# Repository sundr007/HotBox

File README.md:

# HotBox

I use this when I'm testing electronics on my benchtop.  I put this box on top of what I'm testing to raise the ambient temperature.  This is convenient because I can leave my probes and other wires hooked up as is.
This box can raise the ambient temperature up to 55C.

The design consists of a finger edge laser cut acrylic box that has a circuit board assembly mount in the top center of it.  I put foam on the bottom edge of the box so it can nicely sit on top of wires and cables without air gaps.  

The circuit board assembly consists of a 2 layer PCB meant to fit PCBWAY's cheap board special (hint,they're $1 a piece for QTY 5).  On the PCB there is a ST NUCLEO-G431KB board which is an easy way to add a microcontroller.  There's 2 buttons to control temperature setpoint, a 7 segment display to display temperature, a peltier plate that acts as the heating element, and an Intel LGA1155 processor fan to spread the heat from the peltier plate.

I have built the current revision and found that it works as expected and I'm able to use it as I debug and test my electronics.

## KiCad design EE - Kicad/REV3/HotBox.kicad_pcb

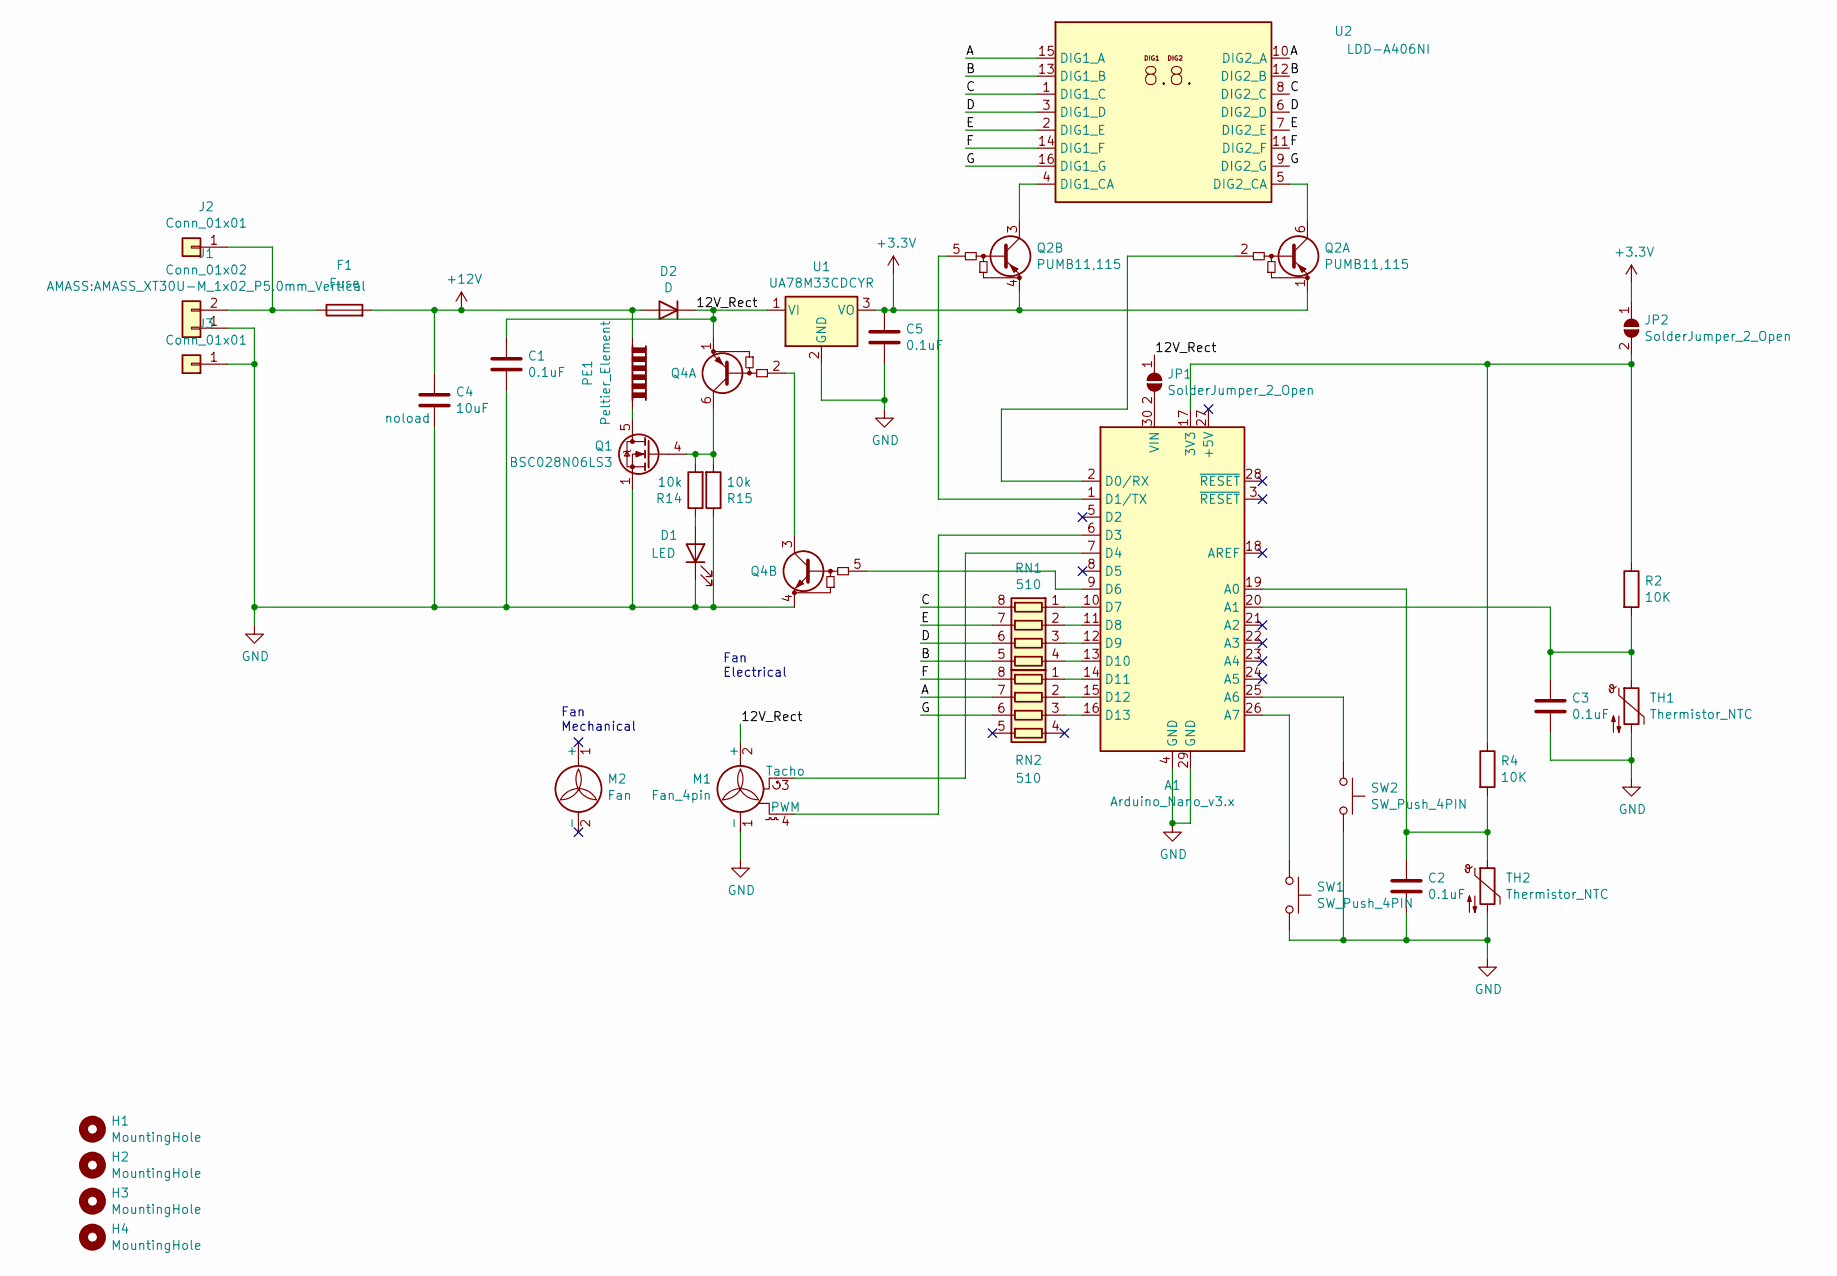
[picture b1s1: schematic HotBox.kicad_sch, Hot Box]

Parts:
A1: Arduino_Nano_v3.x; Arduino_Nano; DigikeyPN 497-19489-ND
C1, C2, C3, C5: 0.1uF; 0805_C; DigikeyPN 478-12790-1-ND
C4: 10uF; CP_Radial_D6.3mm_P2.50mm; DigikeyPN 493-16595-ND
D1: LED; LED_0603_1608Metric; DigikeyPN 732-4978-1-ND
D2: D; D_SMA; DigikeyPN SS13-LTPMSCT-ND
F1: Fuse; R_1206_3216Metric; DigikeyPN SF-1206HH10M-2CT-ND
H1, H2, H3, H4: MountingHole; MountingHole_3.2mm_M3; DigikeyPN 335-1156-ND
J1: Conn_01x02; AMASS_XT30U-M_1x02_P5.0mm_Vertical; DigikeyPN Amass XT30
J2, J3: Conn_01x01; Banana_Jack_1Pin; DigikeyPN 36-575-4-ND
JP1, JP2: SolderJumper_2_Open; SolderJumper-2_P1.3mm_Open_TrianglePad1.0x1.5mm
M1: Fan_4pin; FanPinHeader_1x04_P2.54mm_Vertical; DigikeyPN S1012EC-04-ND
M2: Fan; LGA1155_FAN; DigikeyPN Intel E98290-001
PE1: Peltier_Element; Peltier_40x40; DigikeyPN TEC1-12706
Q1: BSC028N06LS3; TDSON-8-1; DigikeyPN 1727-5435-1-ND
Q2: PUMB11,115; SOT-363_SC-70-6_Handsoldering; DigikeyPN 1727-5230-1-ND
Q4: PUMD3,115; SOT-363_SC-70-6_Handsoldering; DigikeyPN 1727-1984-1-ND
R2, R4: 10K; 0805_R; DigikeyPN 541-4163-1-ND
R14, R15: 10k; 0805_R; DigikeyPN 541-4163-1-ND
RN1, RN2: 510; R_Array_Convex_4x0603; DigikeyPN YC164J-510CT-ND
SW1, SW2: SW_Push_4PIN; SW_D6; DigikeyPN 401-1994-ND
TH1: Thermistor_NTC; 0805_R; DigikeyPN 445-175460-1-ND
TH2: Thermistor_NTC; SolderWire-0.25sqmm_1x02_P4.2mm_D0.65mm_OD1.7mm; DigikeyPN 445-175460-1-ND
U1: UA78M33CDCYR; SOT-223-3_TabPin2; DigikeyPN 296-13424-1-ND
U2: LDD-A406NI; DA04-11CGKWA; DigikeyPN 67-1447-ND

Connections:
+3V3: C5.1, JP2.1 (A), Q2.1 (E1), Q2.4 (E2), U1.3 (VO)
+12V: C4.1, D2.2 (A), F1.2, PE1.1
/12V_Rect: C1.1, D2.1 (K), JP1.1 (A), M1.2 (+), Q4.1 (E1), U1.1 (VI)
/A: RN2.7 (R2.2), U2.10 (DIG2_A), U2.15 (DIG1_A)
/B: RN1.5 (R4.2), U2.12 (DIG2_B), U2.13 (DIG1_B)
/C: RN1.8 (R1.2), U2.1 (DIG1_C), U2.8 (DIG2_C)
/D: RN1.6 (R3.2), U2.3 (DIG1_D), U2.6 (DIG2_D)
/E: RN1.7 (R2.2), U2.2 (DIG1_E), U2.7 (DIG2_E)
/F: RN2.8 (R1.2), U2.11 (DIG2_F), U2.14 (DIG1_F)
/G: RN2.6 (R3.2), U2.9 (DIG2_G), U2.16 (DIG1_G)
GND: A1.4 (GND), A1.29 (GND), C1.2, C2.2, C3.2, C4.2, C5.2, D1.1 (K), J1.1, J3.1, M1.1 (-), Q1.1 (S), Q1.2 (S), Q1.3 (S), Q4.4 (E1), R15.1, SW1.2, SW2.2, TH1.2, TH2.2, U1.2 (GND)
unnamed: A1.1 (D1/TX), Q2.5 (B2)
unnamed: A1.2 (D0/RX), Q2.2 (B1)
unnamed: A1.6 (D3), M1.4 (PWM)
unnamed: A1.7 (D4), M1.3 (Tacho)
unnamed: A1.9 (D6), Q4.5 (B1)
unnamed: A1.10 (D7), RN1.1 (R1.1)
unnamed: A1.11 (D8), RN1.2 (R2.1)
unnamed: A1.12 (D9), RN1.3 (R3.1)
unnamed: A1.13 (D10), RN1.4 (R4.1)
unnamed: A1.14 (D11), RN2.1 (R1.1)
unnamed: A1.15 (D12), RN2.2 (R2.1)
unnamed: A1.16 (D13), RN2.3 (R3.1)
unnamed: A1.17 (3V3), JP2.2 (B), R2.1, R4.1
unnamed: A1.19 (A0), C2.1, R4.2, TH2.1
unnamed: A1.20 (A1), C3.1, R2.2, TH1.1
unnamed: A1.25 (A6), SW2.1
unnamed: A1.26 (A7), SW1.1
unnamed: A1.30 (VIN), JP1.2 (B)
unnamed: D1.2 (A), R14.1
unnamed: F1.1, J1.2, J2.1
unnamed: PE1.2, Q1.5 (D)
unnamed: Q1.4 (G), Q4.6 (C1), R14.2, R15.2
unnamed: Q2.3 (C2), U2.4 (DIG1_CA)
unnamed: Q2.6 (C1), U2.5 (DIG2_CA)
unnamed: Q4.2 (B1), Q4.3 (C1)

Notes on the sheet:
Fan Mechanical
Fan Electrical

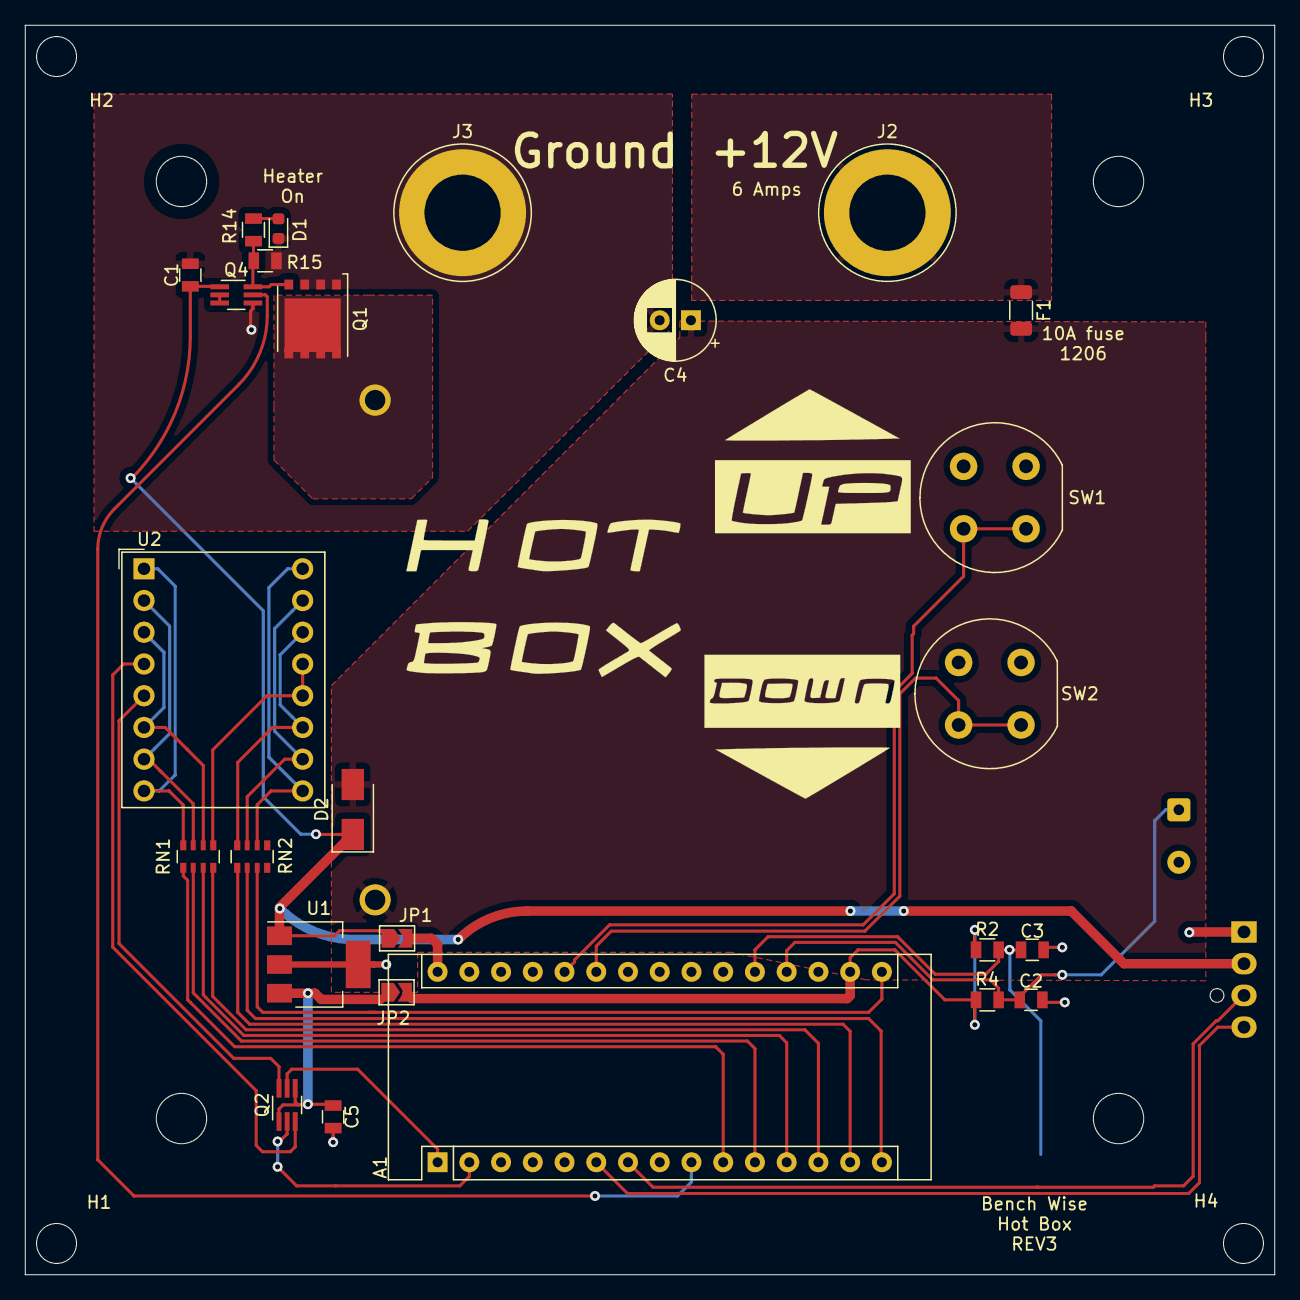
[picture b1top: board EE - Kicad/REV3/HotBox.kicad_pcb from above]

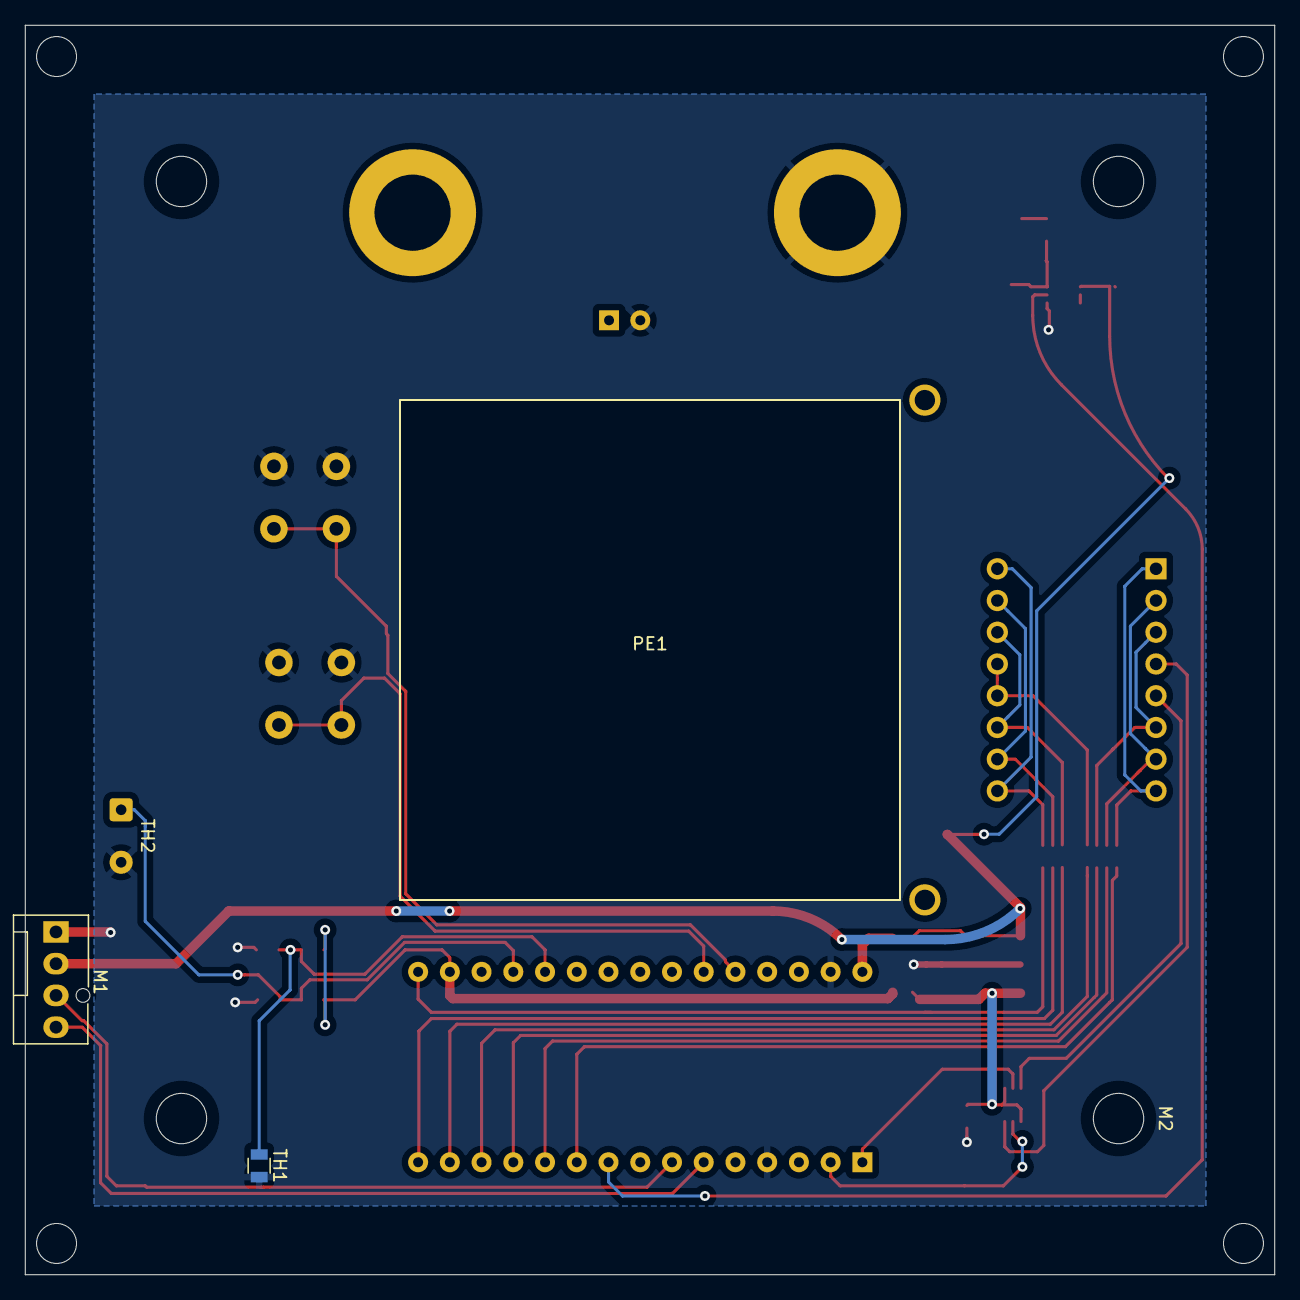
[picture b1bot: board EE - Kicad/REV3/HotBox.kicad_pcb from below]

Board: 2 copper layers, 100.0 x 100.0 mm, 35 parts (5 on the bottom side), 36 nets.

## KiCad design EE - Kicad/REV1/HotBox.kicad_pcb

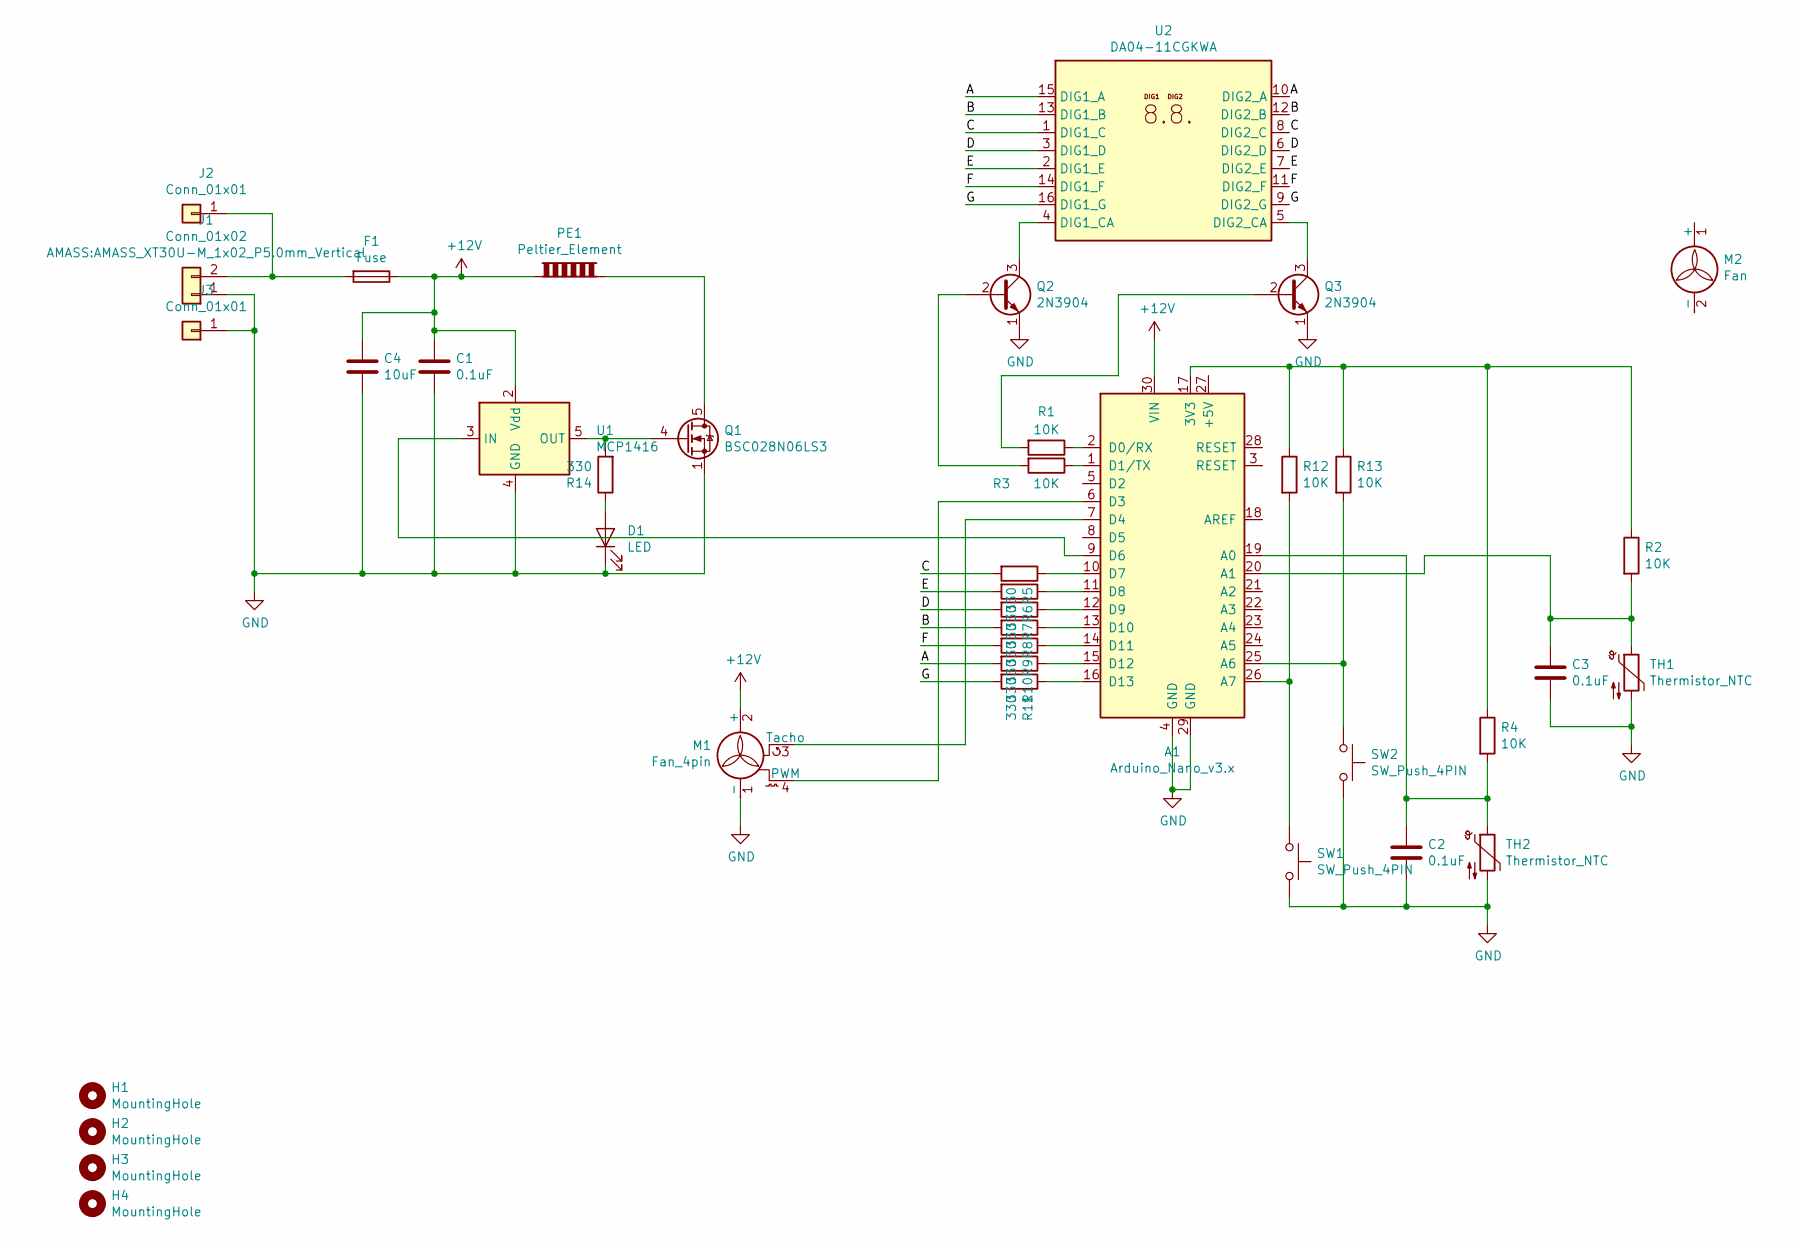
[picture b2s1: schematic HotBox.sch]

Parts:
A1: Arduino_Nano_v3.x; Arduino_Nano
C1, C2, C3: 0.1uF; 0805_C
C4: 10uF; CP_Radial_D6.3mm_P2.50mm
D1: LED; LED_0603_1608Metric
F1: Fuse; 1206_R
H1, H2, H3, H4: MountingHole; MountingHole_3.2mm_M3
J1: Conn_01x02; AMASS_XT30U-M_1x02_P5.0mm_Vertical
J2, J3: Conn_01x01; Banana_Jack_1Pin
M1: Fan_4pin; FanPinHeader_1x04_P2.54mm_Vertical
M2: Fan; LGA1155_FAN
PE1: Peltier_Element; Peltier_40x40
Q1: BSC028N06LS3; TDSON-8-1
Q2, Q3: 2N3904; SOT-23
R1, R2, R3, R4, R12, R13: 10K; 0805_R
R5, R6, R7, R8, R9, R10, R11, R14: 330; 0805_R
SW1, SW2: SW_Push_4PIN; SW_D6; DigikeyPN 401-1994-ND
TH1, TH2: Thermistor_NTC; 0805_R
U1: MCP1416; SOT-23-5
U2: DA04-11CGKWA

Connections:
+12V: A1.30 (VIN), C1.1, C4.1, F1.1, M1.2 (+), PE1.1, U1.2 (Vdd)
/A: R10.2, U2.10 (DIG2_A), U2.15 (DIG1_A)
/B: R8.2, U2.12 (DIG2_B), U2.13 (DIG1_B)
/C: R5.2, U2.1 (DIG1_C), U2.8 (DIG2_C)
/D: R7.2, U2.3 (DIG1_D), U2.6 (DIG2_D)
/E: R6.2, U2.2 (DIG1_E), U2.7 (DIG2_E)
/F: R9.2, U2.11 (DIG2_F), U2.14 (DIG1_F)
/G: R11.2, U2.9 (DIG2_G), U2.16 (DIG1_G)
GND: A1.4 (GND), A1.29 (GND), C1.2, C2.2, C3.2, C4.2, D1.1 (K), J1.1, J3.1, M1.1 (-), Q1.1 (S), Q1.2 (S), Q1.3 (S), Q2.1 (E), Q3.1 (E), SW1.2, SW2.2, TH1.2, TH2.2, U1.4 (GND)
unnamed: A1.1 (D1/TX), R3.1
unnamed: A1.2 (D0/RX), R1.1
unnamed: A1.6 (D3), M1.4 (PWM)
unnamed: A1.7 (D4), M1.3 (Tacho)
unnamed: A1.9 (D6), U1.3 (IN)
unnamed: A1.10 (D7), R5.1
unnamed: A1.11 (D8), R6.1
unnamed: A1.12 (D9), R7.1
unnamed: A1.13 (D10), R8.1
unnamed: A1.14 (D11), R9.1
unnamed: A1.15 (D12), R10.1
unnamed: A1.16 (D13), R11.1
unnamed: A1.17 (3V3), R2.1, R4.1, R12.1, R13.1
unnamed: A1.19 (A0), C2.1, R4.2, TH2.1
unnamed: A1.20 (A1), C3.1, R2.2, TH1.1
unnamed: A1.25 (A6), R13.2, SW2.1
unnamed: A1.26 (A7), R12.2, SW1.1
unnamed: D1.2 (A), R14.1
unnamed: F1.2, J1.2, J2.1
unnamed: PE1.2, Q1.5 (D)
unnamed: Q1.4 (G), R14.2, U1.5 (OUT)
unnamed: Q2.2 (B), R3.2
unnamed: Q2.3 (C), U2.4 (DIG1_CA)
unnamed: Q3.2 (B), R1.2
unnamed: Q3.3 (C), U2.5 (DIG2_CA)

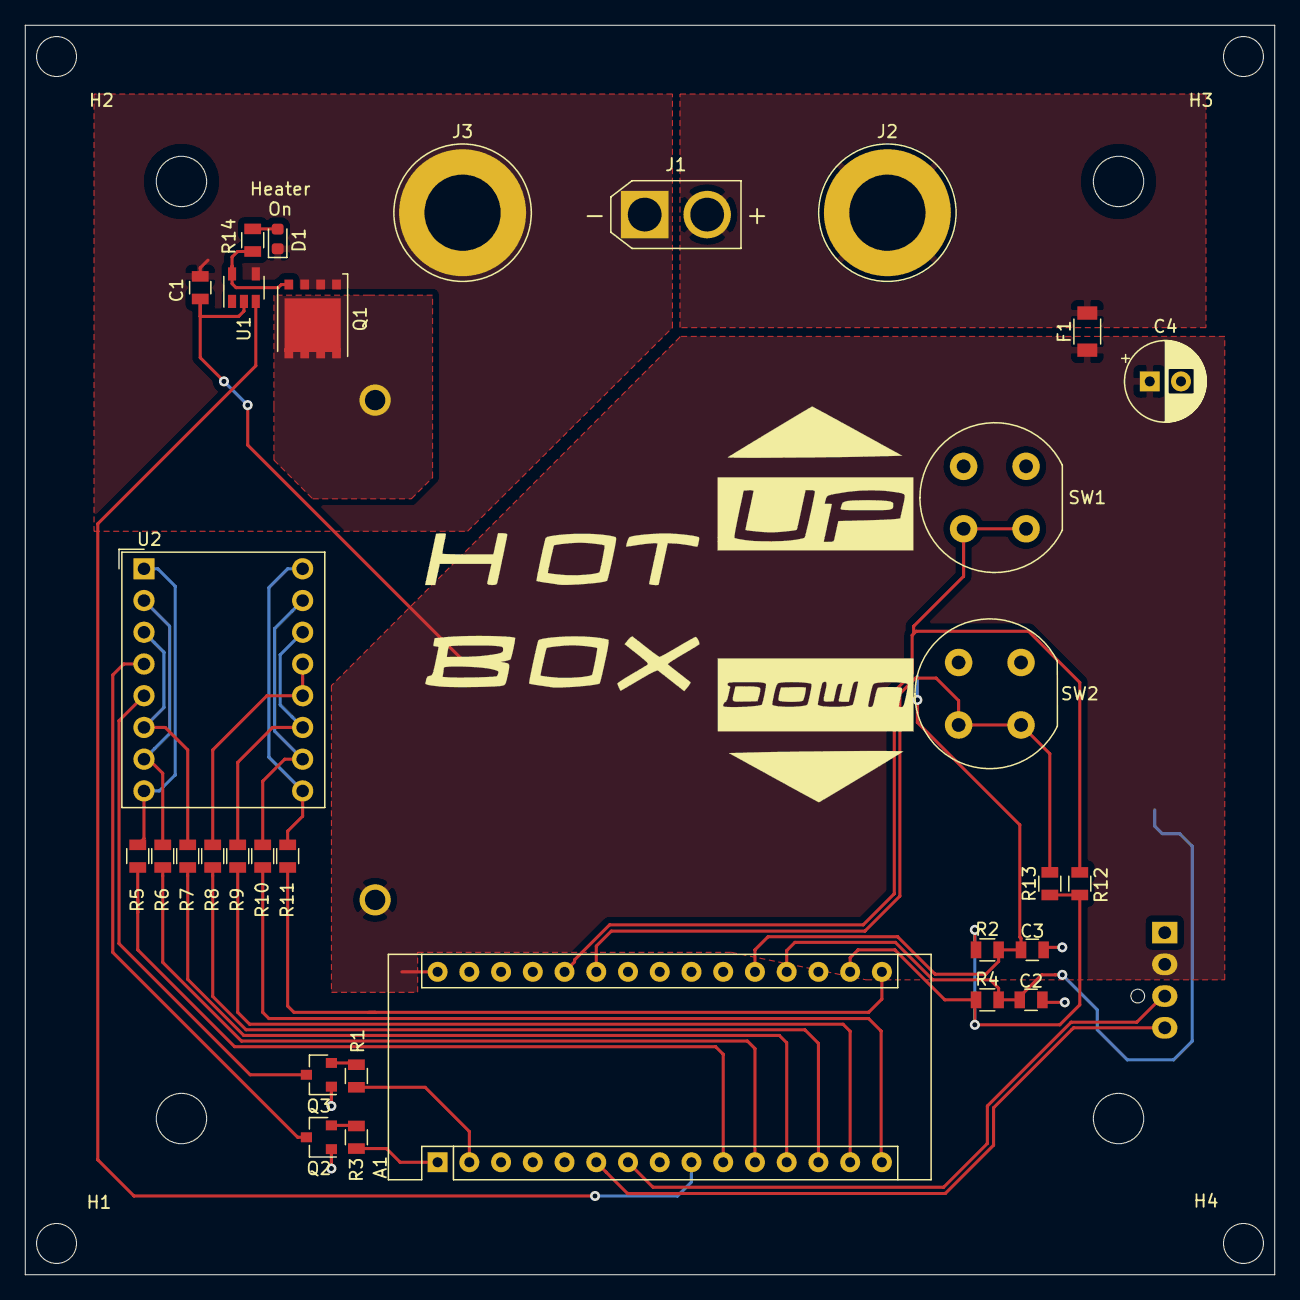
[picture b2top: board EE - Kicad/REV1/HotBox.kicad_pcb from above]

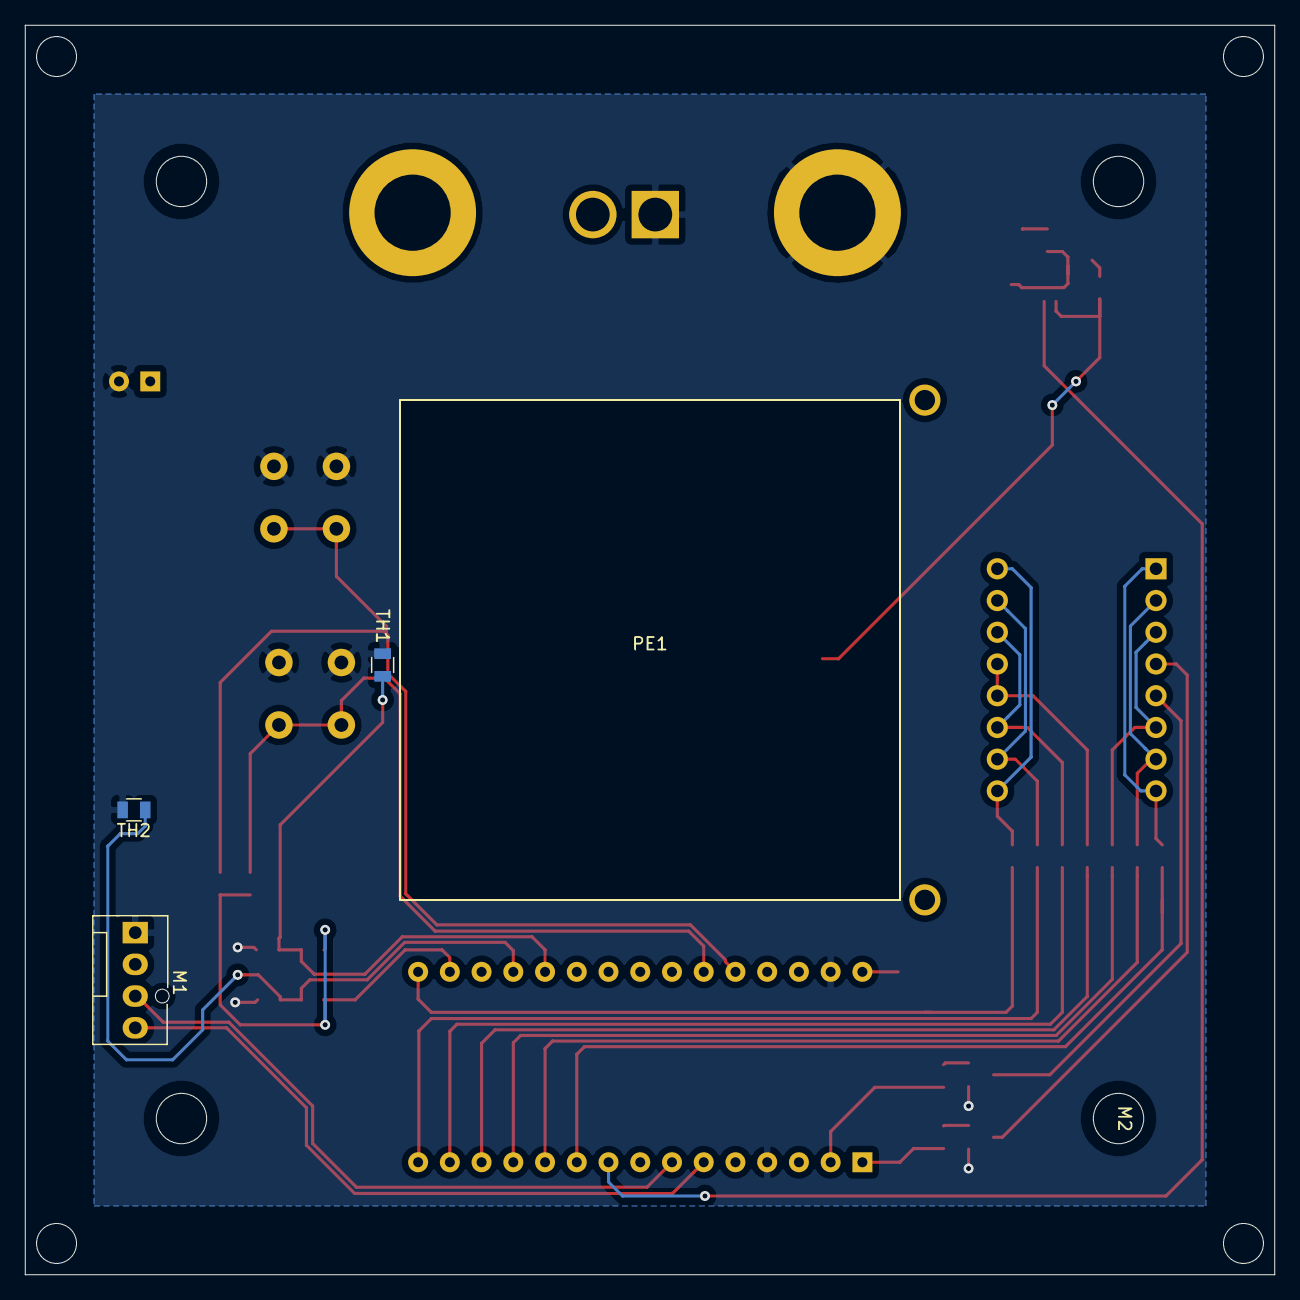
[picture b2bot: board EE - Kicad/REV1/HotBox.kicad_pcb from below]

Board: 2 copper layers, 100.0 x 100.0 mm, 40 parts (5 on the bottom side), 34 nets.

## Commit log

2020-08-28 Initial Commit of design files. STM32 SW place holder added.
2020-08-28 add image
2020-08-28 Add PCB image for MD file.
2020-08-28 Add OpenScad Image
2020-09-06 Add SW Init
2020-09-06 Added Fan PWM Functionality
2020-09-08 Fixed a temperature readback bug. The bug is likely a HW bug, but was fixed by reducing the ADC clock frequency. Because of the low cost nature of the design this is acceptable. Also added floating p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
2020-09-13 Added limits to the temperature setpoint. Slowed the processor clock to reduce power draw.
2020-09-13 Seperated the EE into orderable REVs. Created REV2 based on things that didn't work well in REV1.
2020-09-13 Added the build folder which contains all files necessary to order the physical parts of the design.
2020-12-31 Committing 2nd REV. Update PCB to fix issues with REV1. Reduce mechanical size.
2020-12-31 Add missing files
2020-12-31 Add Build folder
2020-12-31 Remove unneeded files
2020-12-31 Enable pullups on switches. Needed for REV2 HW.
2021-01-03 add Video
2021-01-05 Add .gitattributes to remove c files. The project is really a HW project and not a software project.
2021-01-05 remove .h files
2021-01-05 remove make files
2021-01-05 update video
2021-04-15 Add a build picture of the working REV2
2022-01-25 init commit of REV3 PCB. - adds a fuse - adds reverse polarity protection - moves fan connector so it can clear the fan - changes one NTC to THT so that a flying probe can be used. - add more info in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
